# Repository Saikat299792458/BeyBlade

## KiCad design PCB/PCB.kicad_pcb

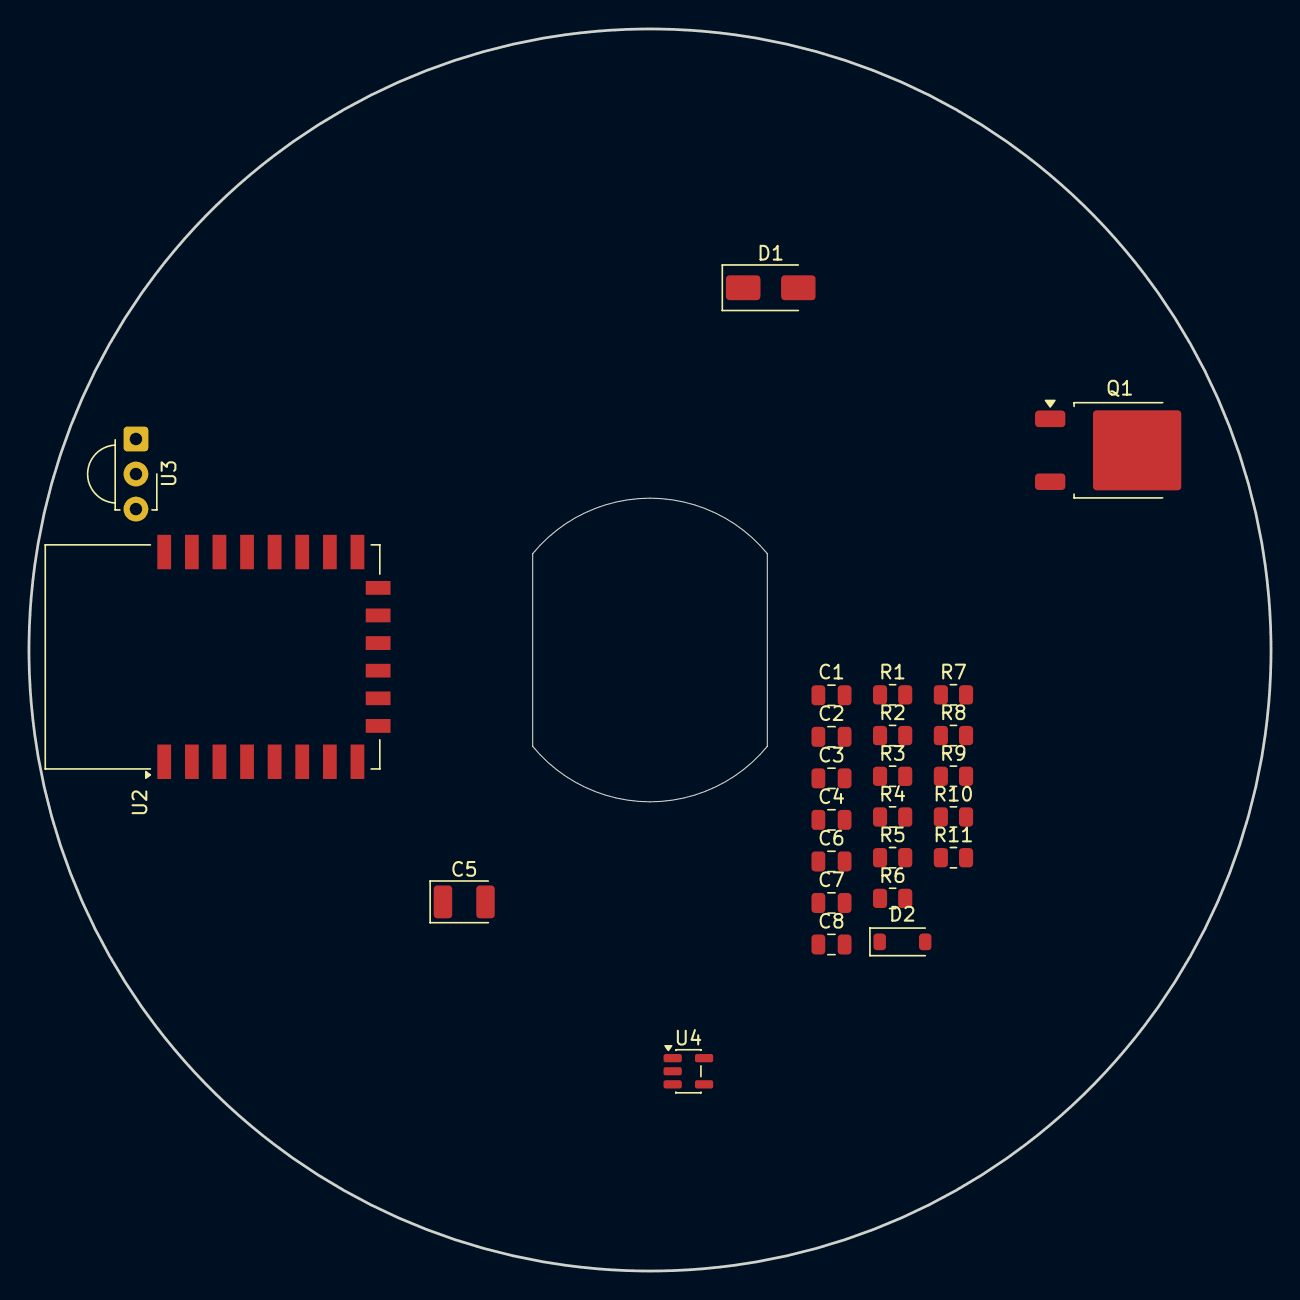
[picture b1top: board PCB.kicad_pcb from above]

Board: 2 copper layers, 90.0 x 90.0 mm, 25 parts (0 on the bottom side), 15 nets, no tracks yet.

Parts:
C1, C2: 10uF; C_0805_2012Metric
C3: 100n Ceramic; C_0805_2012Metric
C4: 100n; C_0805_2012Metric
C5: 22uF Tantalum; CP_EIA-3528-21_Kemet-B
C6: 100nF; C_0805_2012Metric
C7: 4.7uF; C_0805_2012Metric
C8: 0.1uF; C_0805_2012Metric
D1: SS34; D_SMA
D2: D_Zener; D_SOD-123
Q1: IRLZ34NS; TO-252-2
R1, R2, R3, R4, R5, R7, R9: 10k; R_0805_2012Metric
R6, R8: 100; R_0805_2012Metric
R10: 100k; R_0805_2012Metric
R11: 12k; R_0805_2012Metric
U2: ESP-12E
U3: TSOP382xx; Vishay_MINICAST-3Pin
U4: AP2112K-3.3; SOT-23-5

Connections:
+3.3V: C1.1, C3.1, C5.1, R1.1, R2.1, R3.2, R4.2, R8.2, R9.2, U2.8 (VCC), U4.5 (VOUT)
/B3: R6.1, U2.6 (GPIO12)
/B4: R9.1, U2.5 (GPIO14), U3.1 (OUT)
/B5: C8.1, D2.1 (K), R10.2, R11.2, U2.2 (ADC)
GND: C1.2, C2.2, C3.2, C4.1, C4.2, C5.2, C7.2, C8.2, D2.2 (A), Q1.3 (S), R5.2, R7.2, R11.1, U2.15 (GND), U3.2 (GND), U4.2 (GND)
unnamed: C6.2, D1.2 (A), Q1.2 (D)
unnamed: C6.1, D1.1 (K)
unnamed: C2.1, U4.1 (VIN), U4.3 (EN)
unnamed: Q1.1 (G), R6.2, R7.1
unnamed: R1.2, U2.3 (EN)
unnamed: R3.1, U2.18 (GPIO0)
unnamed: R4.1, U2.17 (GPIO2)
unnamed: R5.1, U2.16 (GPIO15)
unnamed: R2.2, U2.1 (~RST)
unnamed: C7.1, R8.1, U3.3 (Vs)
